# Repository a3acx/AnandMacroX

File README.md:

# AnandMacroX
## What is this?
This project is esentially a MacroPad designed with 12 Cherry MX Switches (3 rows and 4 columns) with 4 EC11 Rotary Encoders located under the the switches. This MacroPad also includes an 128x64 OLED display which could be used to display anything from the time and date to performnace statistics of your computer.

## Why did I make this?
When I was playing a video game, I realized that it would be nice if i had some shortcuts to perform certain actions faster. I looked around on the internet and found many suitable options. However, there was a major issue. All of the options that I considered were over $200! That is when I decided that I would try to make my own. And what you see here is that result.

## Pictures

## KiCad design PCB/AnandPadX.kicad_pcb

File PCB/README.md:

In This Folder, you will find the PCB source files fully designed by me in Kicad 9.0

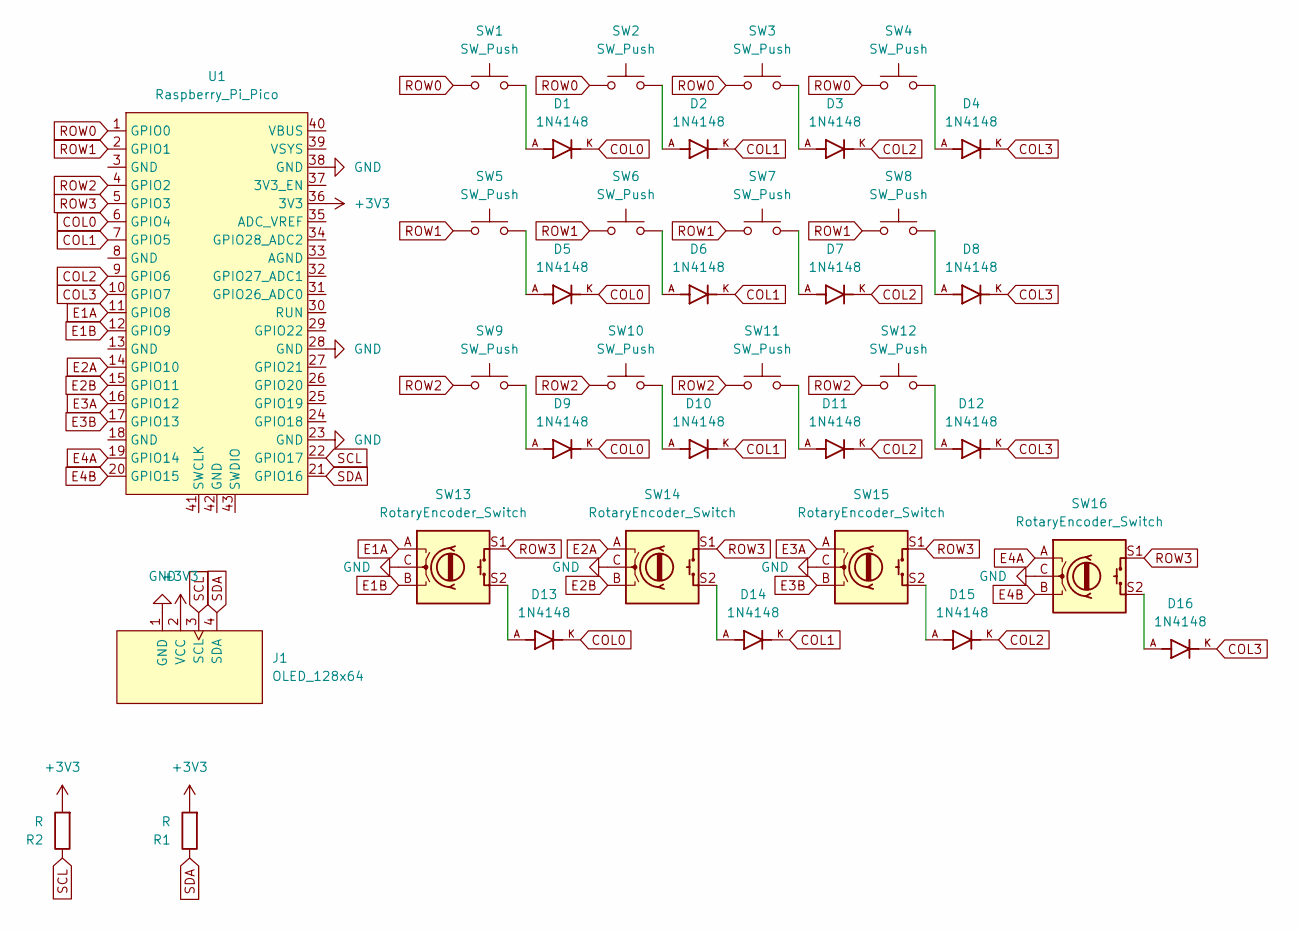
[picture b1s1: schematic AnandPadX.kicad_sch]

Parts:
D1, D2, D3, D4, D5, D6, D7, D8, D9, D10, D11, D12, D13, D14, D15, D16: 1N4148; DIOAD753W49L380D172B; PARTREV 5
J1: OLED_128x64
R1, R2: R; R_Axial_DIN0207_L6.3mm_D2.5mm_P7.62mm_Horizontal
SW1, SW2, SW3, SW4, SW5, SW6, SW7, SW8, SW9, SW10, SW11, SW12: SW_Push; MX_Solder_1.00u
SW13, SW14, SW15, SW16: RotaryEncoder_Switch; Encoder_EC11_MX
U1: Raspberry_Pi_Pico

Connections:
+3V3: J1.2 (VCC), R1.2, R2.2, U1.36 (3V3)
COL0: D1.K, D5.K, D9.K, D13.K, U1.6 (GPIO4)
COL1: D2.K, D6.K, D10.K, D14.K, U1.7 (GPIO5)
COL2: D3.K, D7.K, D11.K, D15.K, U1.9 (GPIO6)
COL3: D4.K, D8.K, D12.K, D16.K, U1.10 (GPIO7)
E1A: SW13.A, U1.11 (GPIO8)
E1B: SW13.B, U1.12 (GPIO9)
E2A: SW14.A, U1.14 (GPIO10)
E2B: SW14.B, U1.15 (GPIO11)
E3A: SW15.A, U1.16 (GPIO12)
E3B: SW15.B, U1.17 (GPIO13)
E4A: SW16.A, U1.19 (GPIO14)
E4B: SW16.B, U1.20 (GPIO15)
GND: J1.1 (GND), SW13.C, SW14.C, SW15.C, SW16.C, U1.23 (GND), U1.28 (GND), U1.38 (GND)
unnamed: D1.A, SW1.2
unnamed: D2.A, SW2.2
unnamed: D3.A, SW3.2
unnamed: D4.A, SW4.2
unnamed: D5.A, SW5.2
unnamed: D6.A, SW6.2
unnamed: D7.A, SW7.2
unnamed: D8.A, SW8.2
unnamed: D9.A, SW9.2
unnamed: D10.A, SW10.2
unnamed: D11.A, SW11.2
unnamed: D12.A, SW12.2
unnamed: D13.A, SW13.S2
unnamed: D14.A, SW14.S2
unnamed: D15.A, SW15.S2
unnamed: D16.A, SW16.S2
ROW0: SW1.1, SW2.1, SW3.1, SW4.1, U1.1 (GPIO0)
ROW1: SW5.1, SW6.1, SW7.1, SW8.1, U1.2 (GPIO1)
ROW2: SW9.1, SW10.1, SW11.1, SW12.1, U1.4 (GPIO2)
ROW3: SW13.S1, SW14.S1, SW15.S1, SW16.S1, U1.5 (GPIO3)
SCL: J1.3 (SCL), R2.1, U1.22 (GPIO17)
SDA: J1.4 (SDA), R1.1, U1.21 (GPIO16)

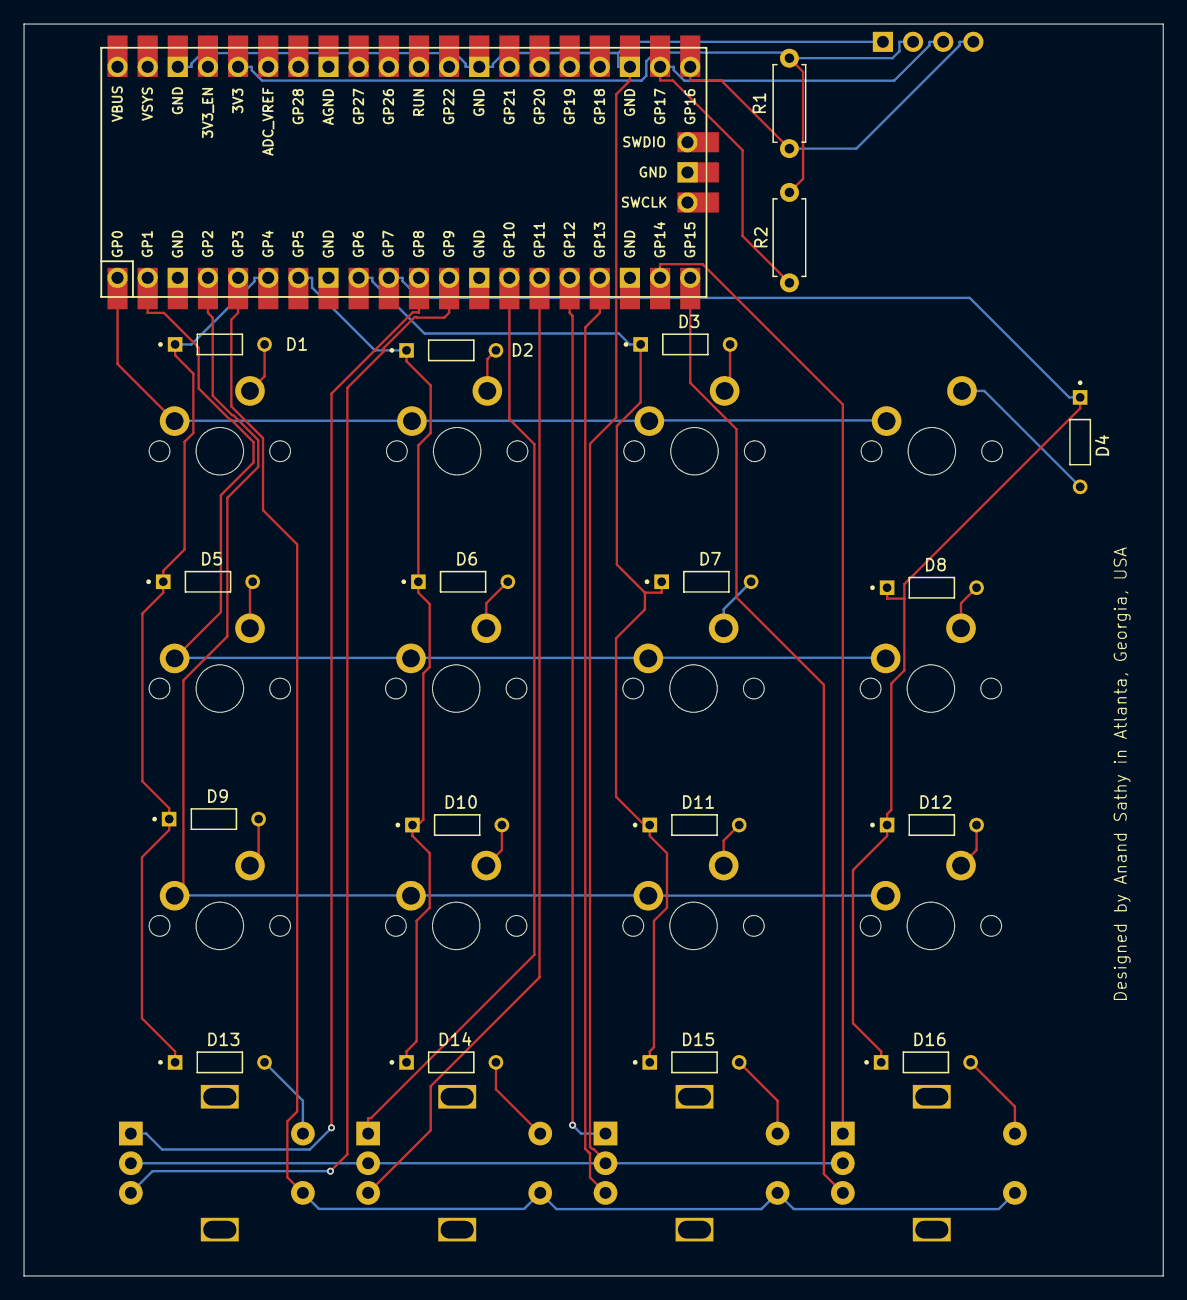
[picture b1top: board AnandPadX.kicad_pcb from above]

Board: 2 copper layers, 96.0 x 105.5 mm, 36 parts (0 on the bottom side), 36 nets.

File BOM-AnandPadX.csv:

"Reference","Value","Datasheet","Footprint","Qty","Link"
"D1,D2,D3,D4,D5,D6,D7,D8,D9,D10,D11,D12,D13,D14,D15,D16","1N4148","","1N4148:DIOAD753W49L380D172B","16","https://www.amazon.com/120Pcs-Rectifier-100Volt-Electronic-S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"
"J1","OLED_128x64","","ScottoKeebs_Components:OLED_128x64","1","https://www.amazon.com/UCTRONICS-SSD1306-Self-Luminous-Displ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"
"R1,R2","R","~","Resistor_THT:R_Axial_DIN0207_L6.3mm_D2.5mm_P7.62mm_Horizontal","2","https://www.amazon.com/BOJACK-Resistors-Carbon-Single-Resist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"
"SW1,SW2,SW3,SW4,SW5,SW6,SW7,SW8,SW9,SW10,SW11,SW12","SW_Push","~","ScottoKeebs_Scotto:MX_Solder_1.00u","12","https://www.amazon.com/Cherry-MX-RGB-Mechanical-Keyboard/dp/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"
"SW13,SW14,SW15,SW16","RotaryEncoder_Switch","~","ScottoKeebs_Scotto:Encoder_EC11_MX","4","https://www.amazon.com/WayinTop-Encoder-Potentiometer-Electr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"
"U1","Raspberry_Pi_Pico","","ScottoKeebs_MCU:Raspberry_Pi_Pico","1","https://www.amazon.com/Pico-Raspberry-Pre-Soldered-Dual-core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"

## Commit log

2025-07-10 Rename image.png to images/PCB-2D.png
2025-07-10 Rename image.png to PCB-3D.png
2025-07-10 Rename image.png to BOM.png
2025-07-12 Update Journal.md (7/11)
